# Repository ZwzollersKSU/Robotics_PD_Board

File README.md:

# Robotics_PD_Board
a power distribution and signal distribution PCB for 3 lb combat robot

added stuff

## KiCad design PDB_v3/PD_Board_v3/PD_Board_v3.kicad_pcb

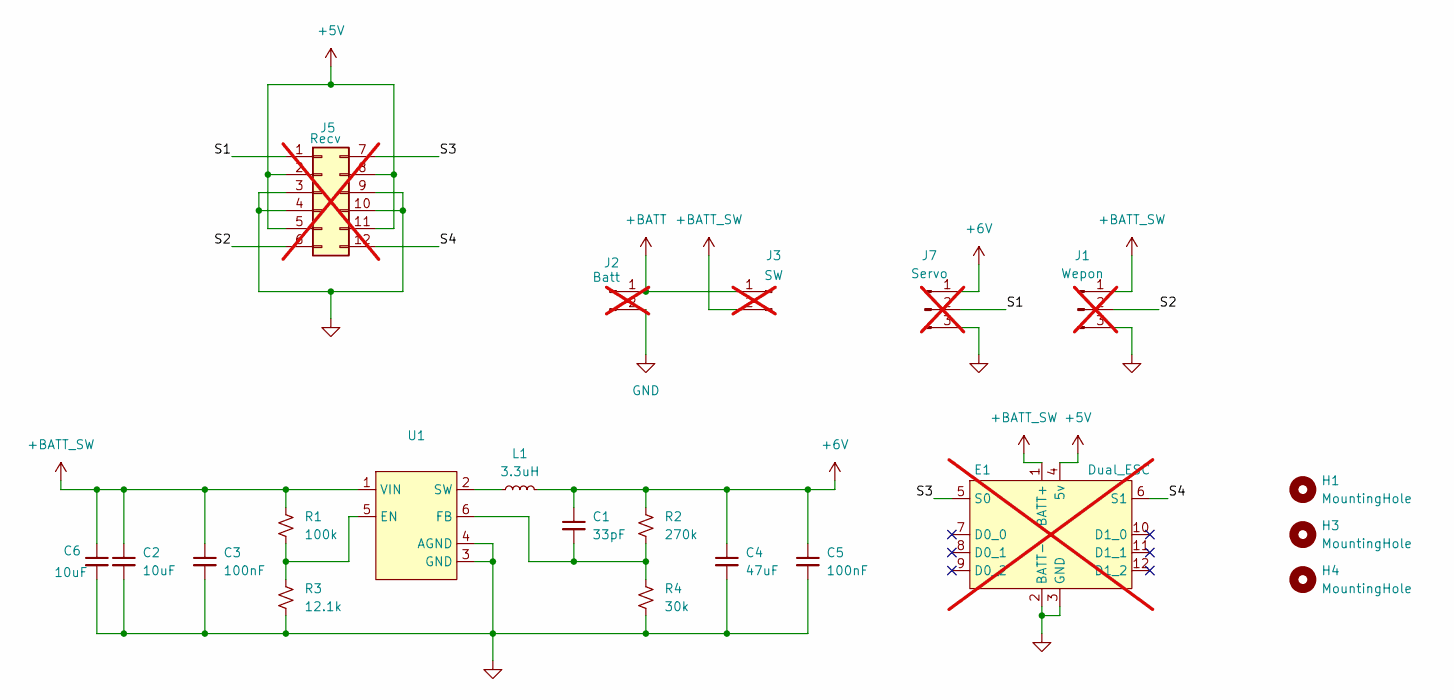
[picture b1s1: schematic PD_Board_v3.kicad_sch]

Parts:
C1: 33pF; C_0805_2012Metric_Pad1.18x1.45mm_HandSolder; Part # 399-C0805C330J3HACTUCT-ND
C2, C6: 10uF; C_0603_1608Metric_Pad1.08x0.95mm_HandSolder; Part # 445-9015-1-ND
C3, C5: 100nF; C_0805_2012Metric_Pad1.18x1.45mm_HandSolder; Part # 399-C0805F104K1RACAUTOCT-ND
C4: 47uF; C_1210_3225Metric_Pad1.33x2.70mm_HandSolder; Part # 490-6539-1-ND
E1: Dual_ESC; not fitted
H1, H3, H4: MountingHole; MountingHole_3.5mm
J1: Wepon; MR30; not fitted
J2: Batt; XT30; not fitted
J3: SW; SMD_SW; not fitted
J5: Recv; PinHeader_2x06_P2.54mm_Horizontal; not fitted
J7: Servo; MR30; not fitted
L1: 3.3uH; Inductor; Part # 2037-VAMV1009AA-3R3MM2CT-ND
R1: 100k; R_0805_2012Metric_Pad1.20x1.40mm_HandSolder; Part # P100KDACT-ND
R2: 270k; R_0805_2012Metric_Pad1.20x1.40mm_HandSolder; Part # P270KDACT-ND
R3: 12.1k; R_0805_2012Metric_Pad1.20x1.40mm_HandSolder; Part # P12.1KDACT-ND
R4: 30k; R_0805_2012Metric_Pad1.20x1.40mm_HandSolder; Part # P30KDACT-ND
U1: SOT-23-6; Part # 296-TPS565247DRLRCT-ND

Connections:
+5V: E1.4 (5v), J5.2, J5.5, J5.8, J5.11
+6V: C1.1, C4.1, C5.1, J7.1, L1.2, R2.1
+BATT: J2.1, J3.1
+BATT_SW: C2.1, C3.1, C6.1, E1.1 (BATT+), J1.1, J3.2, R1.1, U1.1 (VIN)
/S1: J5.1, J7.2
/S2: J1.2, J5.6
/S3: E1.5 (S0), J5.7
/S4: E1.6 (S1), J5.12
GND: C2.2, C3.2, C4.2, C5.2, C6.2, E1.2 (BATT-), E1.3 (GND), J1.3, J2.2, J5.3, J5.4, J5.9, J5.10, J7.3, R3.2, R4.2, U1.3 (GND), U1.4 (AGND)
unnamed: R1.2, R3.1, U1.5 (EN)
unnamed: C1.2, R2.2, R4.1, U1.6 (FB)
unnamed: L1.1, U1.2 (SW)

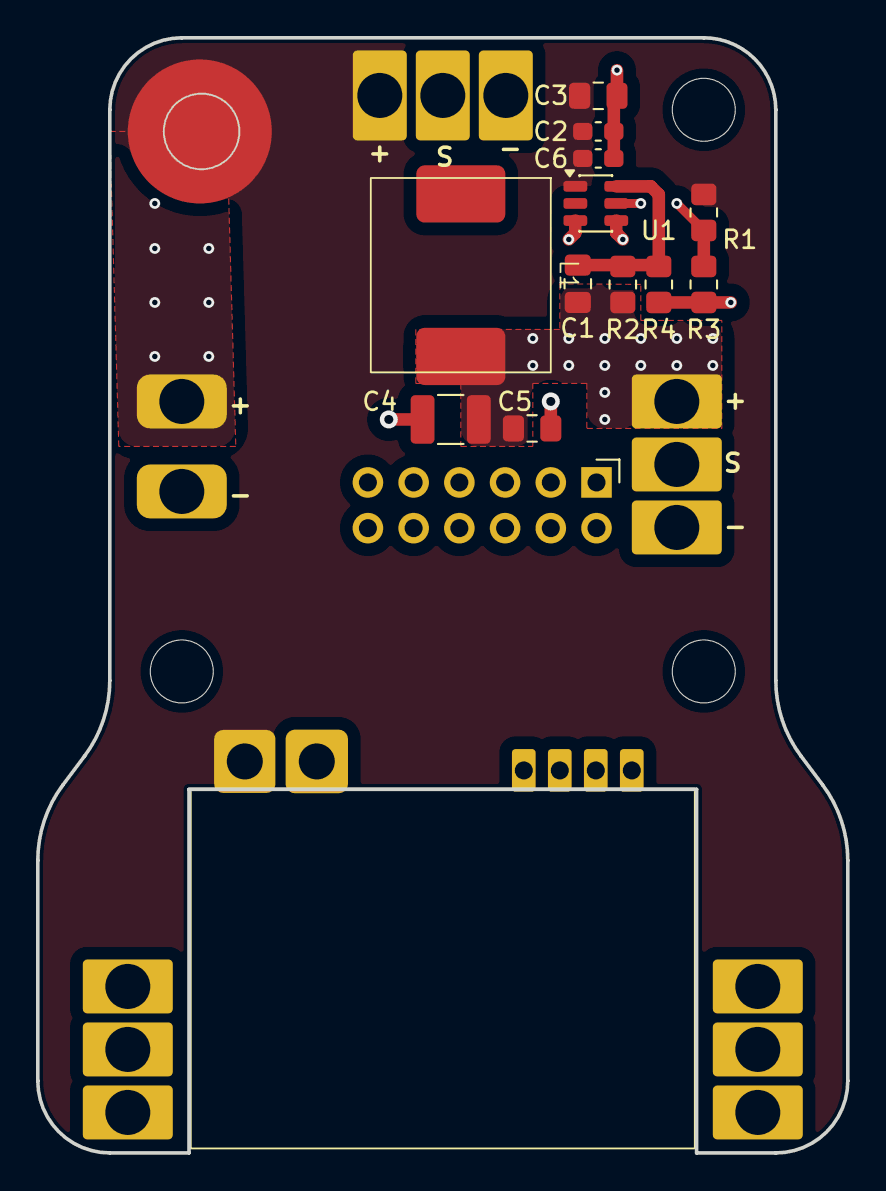
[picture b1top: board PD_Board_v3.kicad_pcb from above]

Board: 4 copper layers, 45.0 x 62.0 mm, 21 parts (0 on the bottom side), 12 nets.

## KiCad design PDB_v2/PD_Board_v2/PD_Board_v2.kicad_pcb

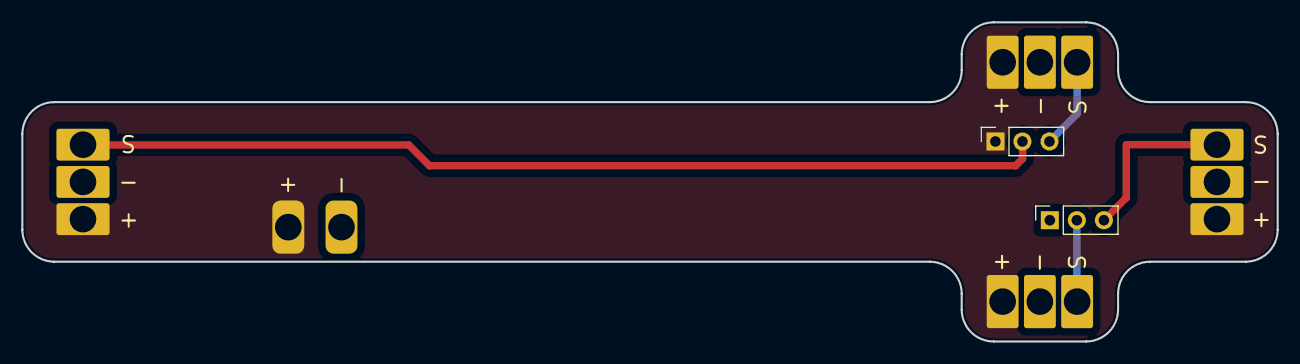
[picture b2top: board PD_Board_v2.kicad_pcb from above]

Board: 2 copper layers, 118.0 x 30.0 mm, 7 parts (0 on the bottom side), 6 nets.

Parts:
J1, J2, J3, J4: MR30
J5, J6: Conn_01x03_Socket; PinSocket_1x03_P2.54mm_Vertical
T1: XT30

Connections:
unnamed: J1.3, J2.3, J3.3, J4.3, J5.1, T1.1 (+)
unnamed: J4.1, J5.2
unnamed: J2.1, J5.3
unnamed: J1.2, J2.2, J3.2, J4.2, J6.1, T1.2 (-)
unnamed: J3.1, J6.2
unnamed: J1.1, J6.3

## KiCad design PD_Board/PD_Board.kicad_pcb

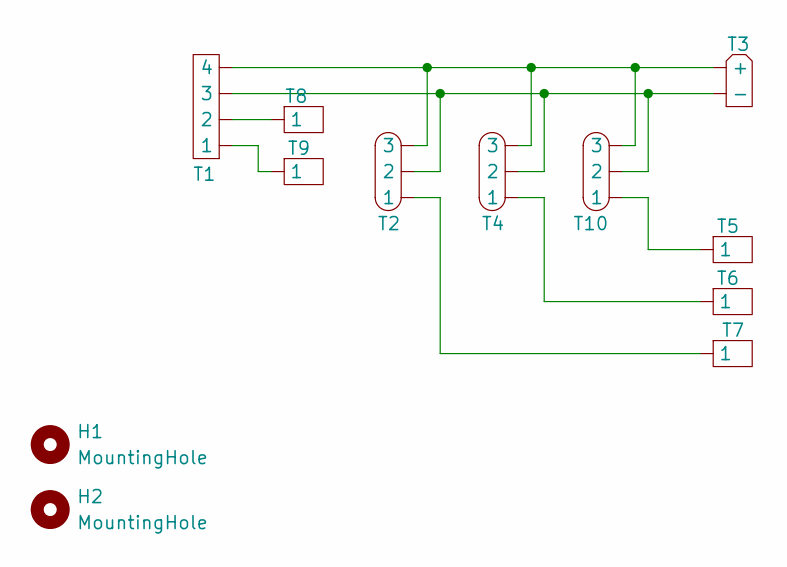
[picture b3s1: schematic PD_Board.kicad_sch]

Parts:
H1, H2: MountingHole; MountingHole_3.2mm_M3_Pad
T1: 2.54x4_Pad
T2, T4, T10: MR30
T3: XT30
T5, T6, T7, T8, T9: Wire_Pad

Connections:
unnamed: T1.1, T9.1
unnamed: T1.2, T8.1
unnamed: T2.1, T7.1
unnamed: T1.4, T2.3, T3.1 (+), T4.3, T10.3
unnamed: T1.3, T2.2, T3.2 (-), T4.2, T10.2
unnamed: T4.1, T6.1
unnamed: T5.1, T10.1

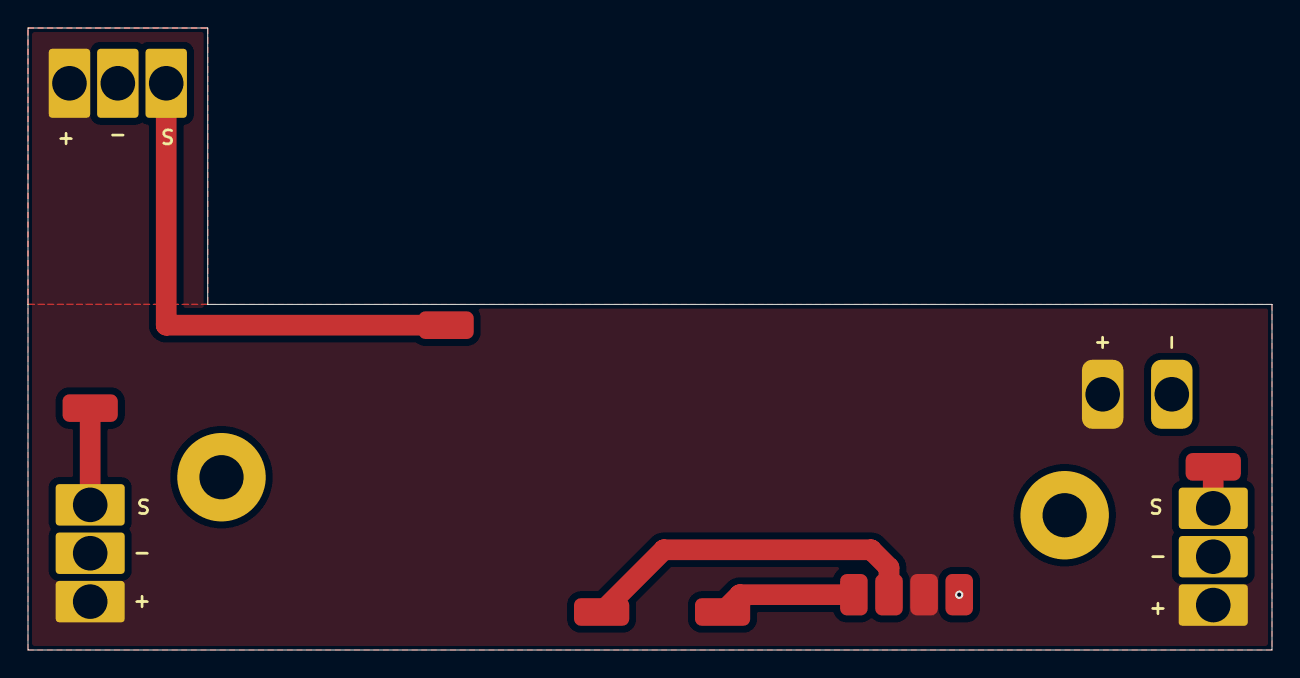
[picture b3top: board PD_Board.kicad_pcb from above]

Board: 2 copper layers, 90.0 x 45.0 mm, 12 parts (0 on the bottom side), 7 nets.

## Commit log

2024-10-24 added kicad project
2024-10-24 added footprints
2024-10-25 started schematic layout
2024-10-30 Removed 2 screw mounts
2024-11-08 womp womp
2025-01-24 Added wing onto pcb for weapon ese
2025-01-24 Created drill files
2025-02-26 v1 and v2 folders made
2025-03-28 'Completed' Board v2
2025-10-22 asdkdjhas
2025-10-22 started the board
2025-11-03 inital route
2025-11-05 almost done
